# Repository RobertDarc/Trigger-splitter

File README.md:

# Trigger-splitter
Spit optical to digital

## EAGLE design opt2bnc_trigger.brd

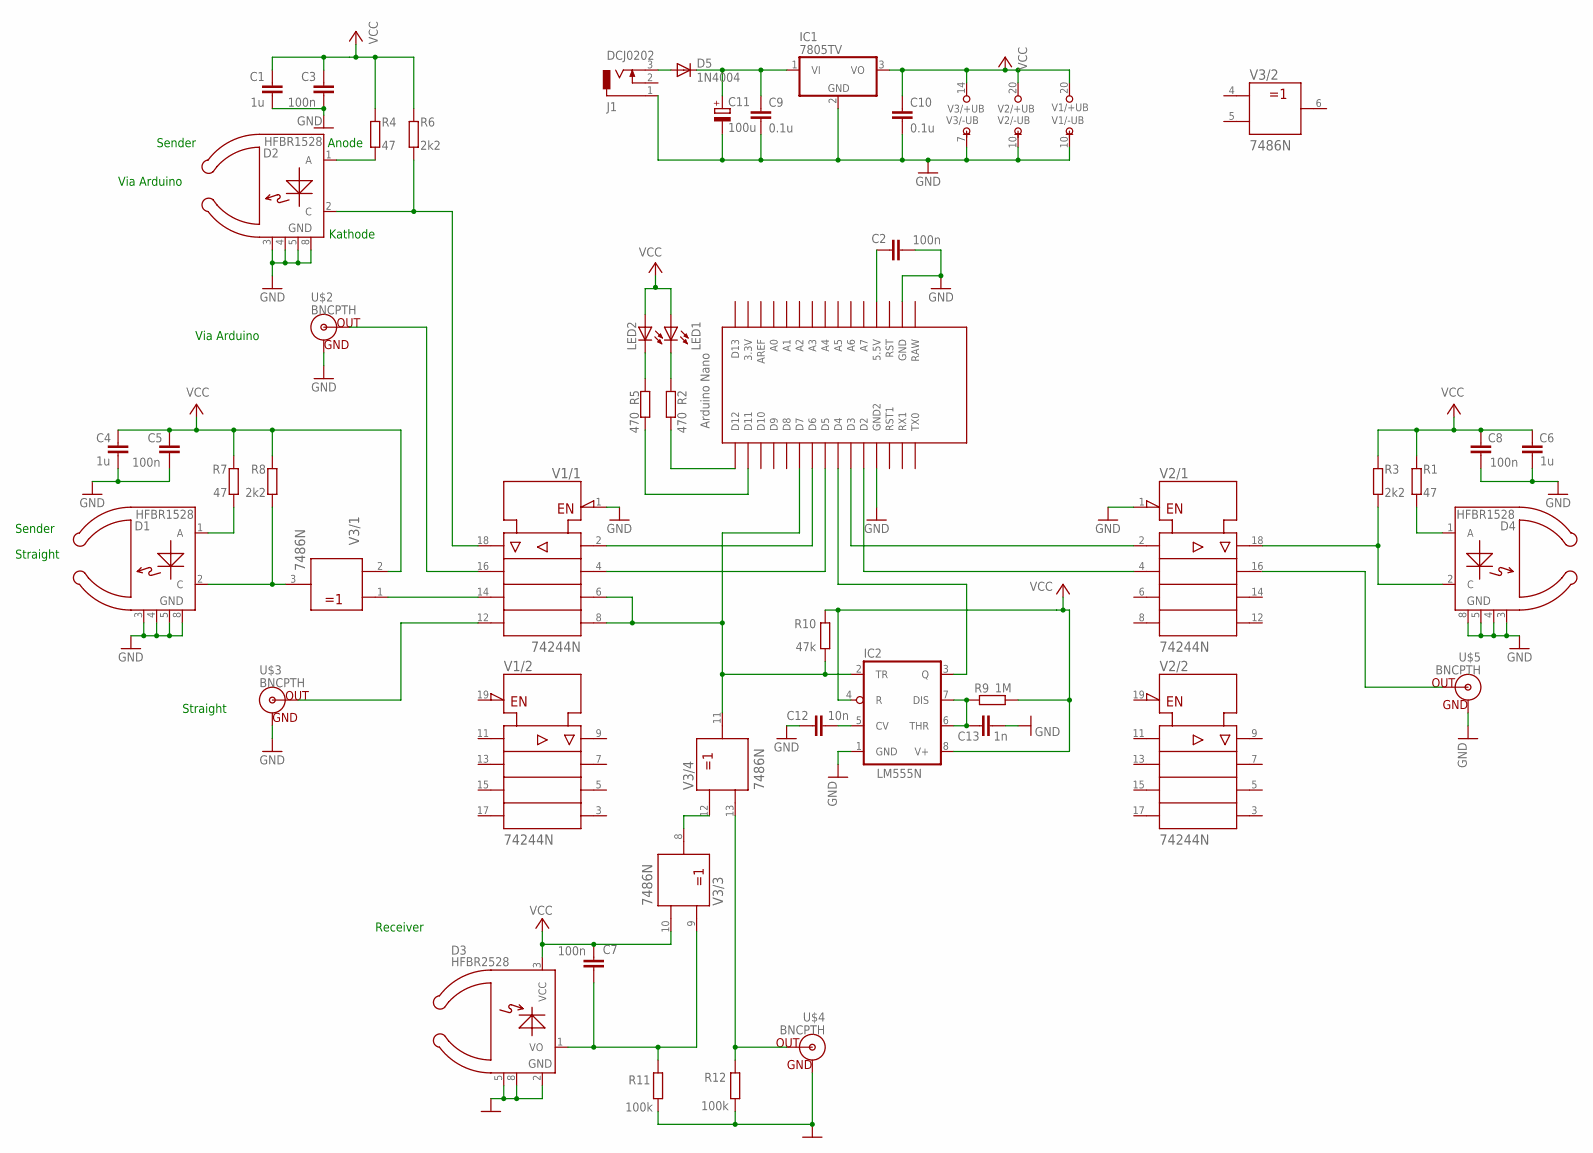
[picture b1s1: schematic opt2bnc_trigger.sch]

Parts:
C1, C4, C6: 1u; C025-025X050
C2, C3, C5, C7, C8: 100n; C025-025X050
C9, C10: 0.1u; C025-024X044
C11: 100u; E2-4
C12: 10n; C025-025X050
C13: 1n; C025-025X050
D1, D2, D4: HFBR1528; HFBR25XX
D3: HFBR2528; HFBR25XX
D5: 1N4004; DO41-10
IC1: 7805TV; TO220V
IC2: LM555N; DIL08
J1: DCJ0202
LED1, LED2: LED3MM
R1, R4, R7: 47; 0207/7
R2, R5: 470; 0207/7
R3, R6, R8: 2k2; 0207/7
R9: 1M; 0207/7
R10: 47k; 0207/7
R11, R12: 100k; 0207/7
U$1: NANO
U$2, U$3, U$4, U$5: BNCPTH; BNC
V1, V2: 74244N; DIL20
V3: 7486N; DIL14

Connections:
GND: C1.2, C2.2, C3.2, C4.2, C5.2, C6.2, C8.2, C9.2, C10.2, C11.-, C12.1, C13.2, D1.3 (1), D1.4, D1.5 (GND), D1.8 (GND), D2.3 (1), D2.4, D2.5 (GND), D2.8 (GND), D3.2 (GND), D3.5 (1), D3.8 (4), D4.3 (1), D4.4, D4.5 (GND), D4.8 (GND), IC1.2 (GND), IC2.1 (GND), J1.1, R11.2, R12.2, U$1.GND, U$1.GND1 (GND2), U$2.GND, U$3.GND, U$4.GND, U$5.GND, V1.1 (!G), V1.10 (-UB), V2.1 (!G), V2.10 (-UB), V3.7 (-UB)
unnamed: C9.1, C11.+, D5.C, IC1.1 (VI)
unnamed: IC2.2 (TR), R10.2, U$1.D7, V1.6 (A3), V1.8 (A4), V3.11 (Y)
unnamed: D2.2 (C), R6.1, V1.18 (Y1)
unnamed: LED1.K (C), R2.1
unnamed: U$1.D6, V1.2 (A1)
unnamed: U$2.S (OUT), V1.16 (Y2)
unnamed: U$1.D5, V1.4 (A2)
unnamed: LED2.K (C), R5.1
unnamed: C7.1, D3.1 (VO), R11.1, V3.9 (A)
unnamed: D2.1 (A), R4.1
unnamed: D5.A, J1.3
unnamed: R2.2, U$1.D12
unnamed: R5.2, U$1.D11
unnamed: D1.1 (A), R7.1
unnamed: U$3.S (OUT), V1.12 (Y4)
unnamed: C2.1, U$1.5V (5.5V)
unnamed: U$1.D2, V2.4 (A2)
unnamed: U$1.D3, V2.2 (A1)
unnamed: D1.2 (C), R8.1, V3.3 (Y)
unnamed: U$5.S (OUT), V2.16 (Y2)
unnamed: D4.1 (A), R1.1
unnamed: D4.2 (C), R3.1, V2.18 (Y1)
unnamed: R12.1, U$4.S (OUT), V3.13 (B)
unnamed: V3.8 (Y), V3.12 (A)
unnamed: C12.2, IC2.5 (CV)
unnamed: C13.1, IC2.6 (THR), IC2.7 (DIS), R9.2
unnamed: IC2.3 (Q), U$1.D4
unnamed: V1.14 (Y3), V3.1 (A)
VCC: C1.1, C3.1, C4.1, C5.1, C6.1, C7.2, C8.1, C10.1, D3.3 (VCC), IC1.3 (VO), IC2.4 (R), IC2.8 (V+), LED1.A, LED2.A, R1.2, R3.2, R4.2, R6.2, R7.2, R8.2, R9.1, R10.1, V1.20 (+UB), V2.20 (+UB), V3.2 (B), V3.10 (B), V3.14 (+UB)

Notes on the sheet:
Anode
Kathode
Receiver
Sender
Via Arduino
Straight

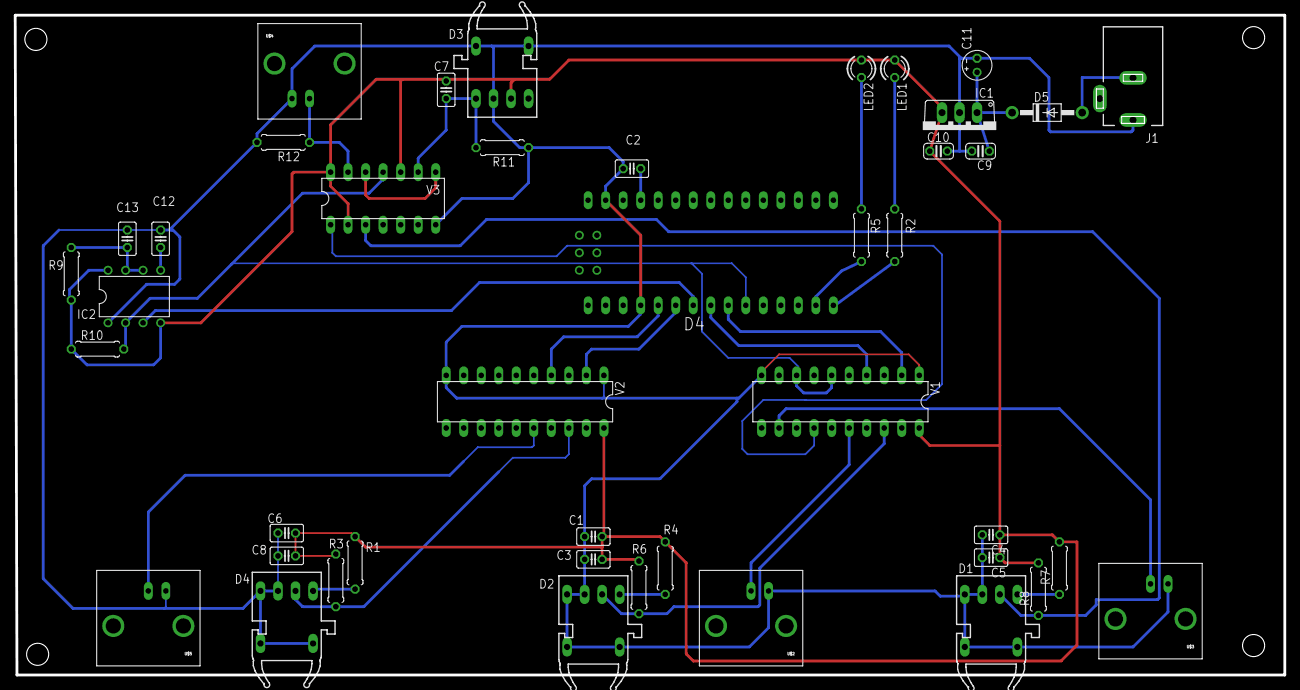
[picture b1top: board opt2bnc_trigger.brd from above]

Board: 2 copper layers, 184.1 x 95.7 mm, 43 parts (0 on the bottom side), 30 nets.
